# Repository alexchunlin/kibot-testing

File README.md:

<h1 align="center">EncoGo</h1>

<p align="center" width="100%">
  
</p>

***

<p align="center">
  
&nbsp; &nbsp; &nbsp; &nbsp;
  
</p>

***

## SPECIFICATIONS

| Parameter | Value | 
| --- | --- |
| Dimensions | 40.0 × 40.0 mm |

***

## DIRECTORY STRUCTURE

    .
    ├─ Computations       # Misc calculations
    ├─ HTML               # HTML files for generated webpage
    ├─ Images             # Pictures and renders
    │
    ├─ kibot_resources    # External resources for KiBot
    │  ├─ colors          # Color theme for KiCad
    │  ├─ fonts           # Fonts used in the project
    │  ├─ scripts         # External scripts used with KiBot
    │  └─ templates       # Templates for KiBot generated reports
    │
    ├─ kibot_yaml         # KiBot YAML config files
    ├─ KiRI               # KiRI (PCB diff viewer) files
    │
    ├─ lib                # KiCad footprint and symbol libraries
    │  ├─ 3d_models       # Component 3D models
    │  ├─ lib_fp          # Footprint libraries
    │  └─ lib_sym         # Symbol libraries
    │
    ├─ Logos              # Logos
    │
    ├─ Manufacturing      # Assembly and fabrication documents
    │  ├─ Assembly        # Assembly documents (BoM, pos, notes)
    │  │
    │  └─ Fabrication     # Fabrication documents (ZIP, notes)
    │     ├─ Drill Tables # CSV drill tables
    │     └─ Gerbers      # Gerbers
    │
    ├─ Report             # Reports for ERC/DRC
    ├─ Schematic          # PDF of schematic
    ├─ Templates          # Title block templates
    ├─ Testing
    │  └─ Testpoints      # Testpoints tables      
    │
    └─ Variants           # Outputs for assembly variants

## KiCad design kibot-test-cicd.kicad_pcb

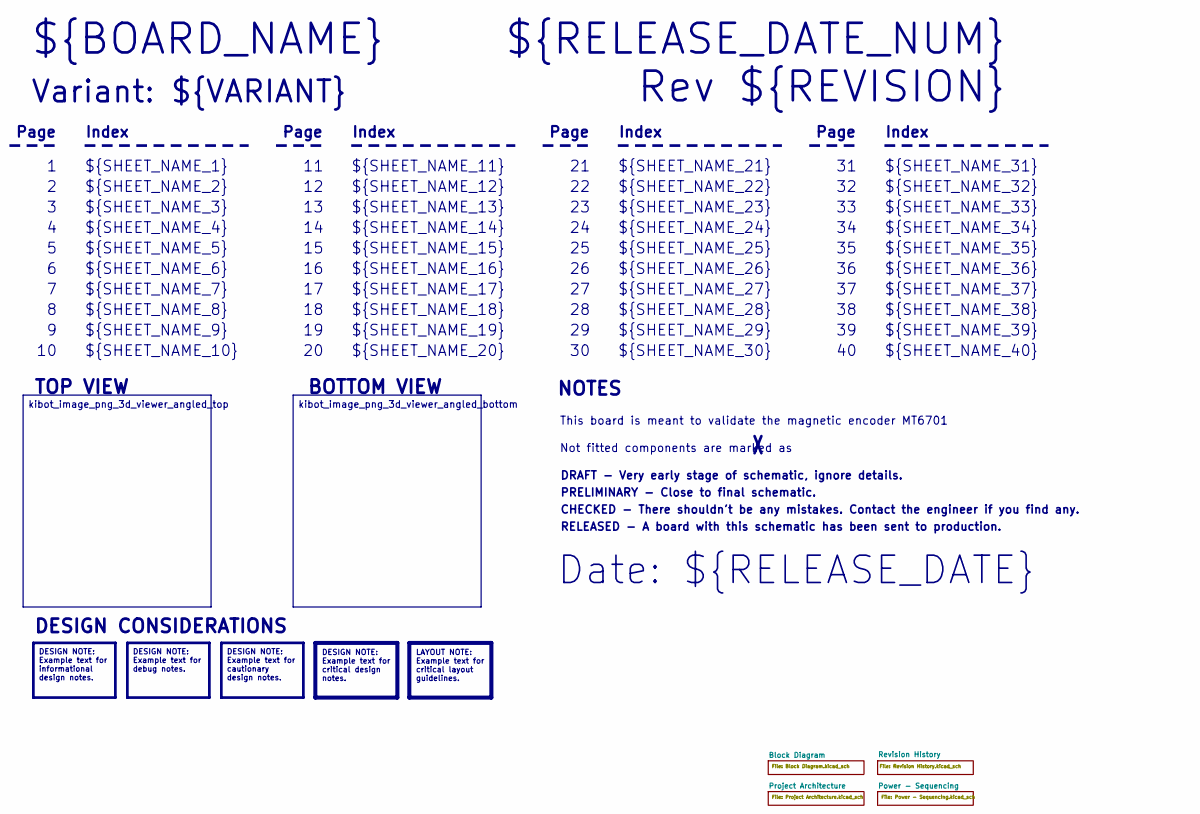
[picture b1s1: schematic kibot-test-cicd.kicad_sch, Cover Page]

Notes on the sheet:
Variant: ${VARIANT}
RELEASED - A board with this schematic has been sent to production.
${SHEET_NAME_24}
Index
Page
PRELIMINARY - Close to final schematic.
${SHEET_NAME_22}
DRAFT - Very early stage of schematic, ignore details.
${SHEET_NAME_12}
${SHEET_NAME_8}
${SHEET_NAME_2}
${SHEET_NAME_5}
${SHEET_NAME_20}
${SHEET_NAME_23}
${RELEASE_DATE_NUM}
${SHEET_NAME_35}
Not fitted components are marked as
${SHEET_NAME_11}
${SHEET_NAME_6}
${SHEET_NAME_37}
${SHEET_NAME_26}
${SHEET_NAME_36}
Rev ${REVISION}
${SHEET_NAME_15}
CHECKED - There shouldn't be any mistakes. Contact the engineer if you find any.
BOTTOM VIEW
${SHEET_NAME_14}
${SHEET_NAME_21}
${SHEET_NAME_17}
${SHEET_NAME_18}
Date: ${RELEASE_DATE}
${SHEET_NAME_7}
${SHEET_NAME_31}
${BOARD_NAME}
NOTES
${SHEET_NAME_40}
${SHEET_NAME_39}
${SHEET_NAME_32}
${SHEET_NAME_1}
${SHEET_NAME_9}

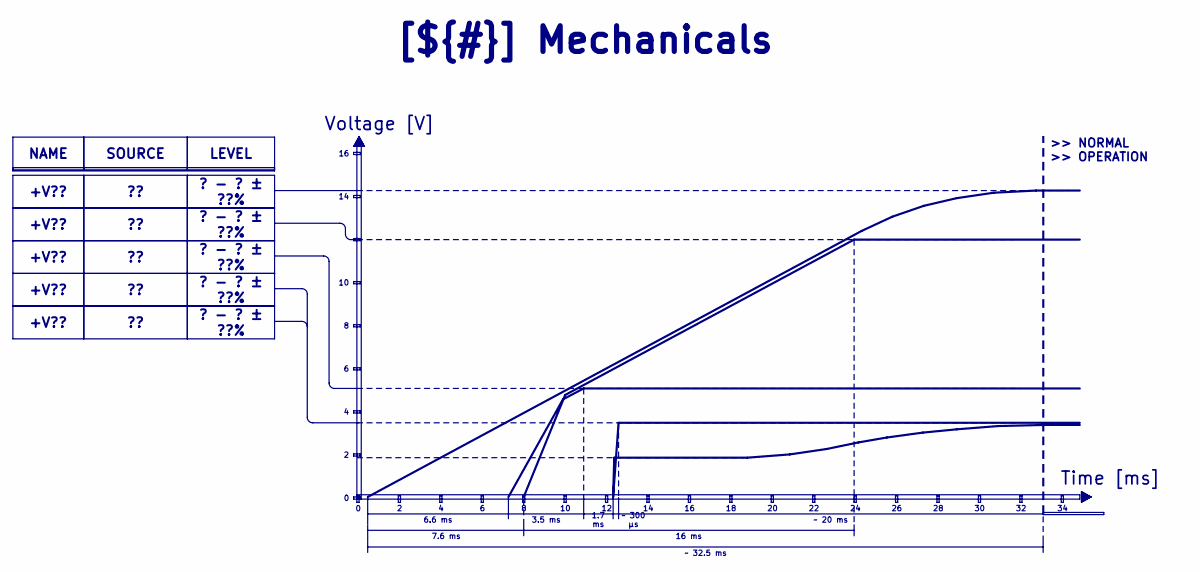
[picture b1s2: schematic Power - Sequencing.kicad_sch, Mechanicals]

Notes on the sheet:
Voltage [V]
>> NORMAL >> OPERATION
Time [ms]
3.5 ms
7.6 ms
? - ? ± ??%
~ 300 μs
1.7 ms
16 ms
+V??
LEVEL
NAME
~ 20 ms
SOURCE
[${#}] ${TITLE}
6.6 ms
~ 32.5 ms

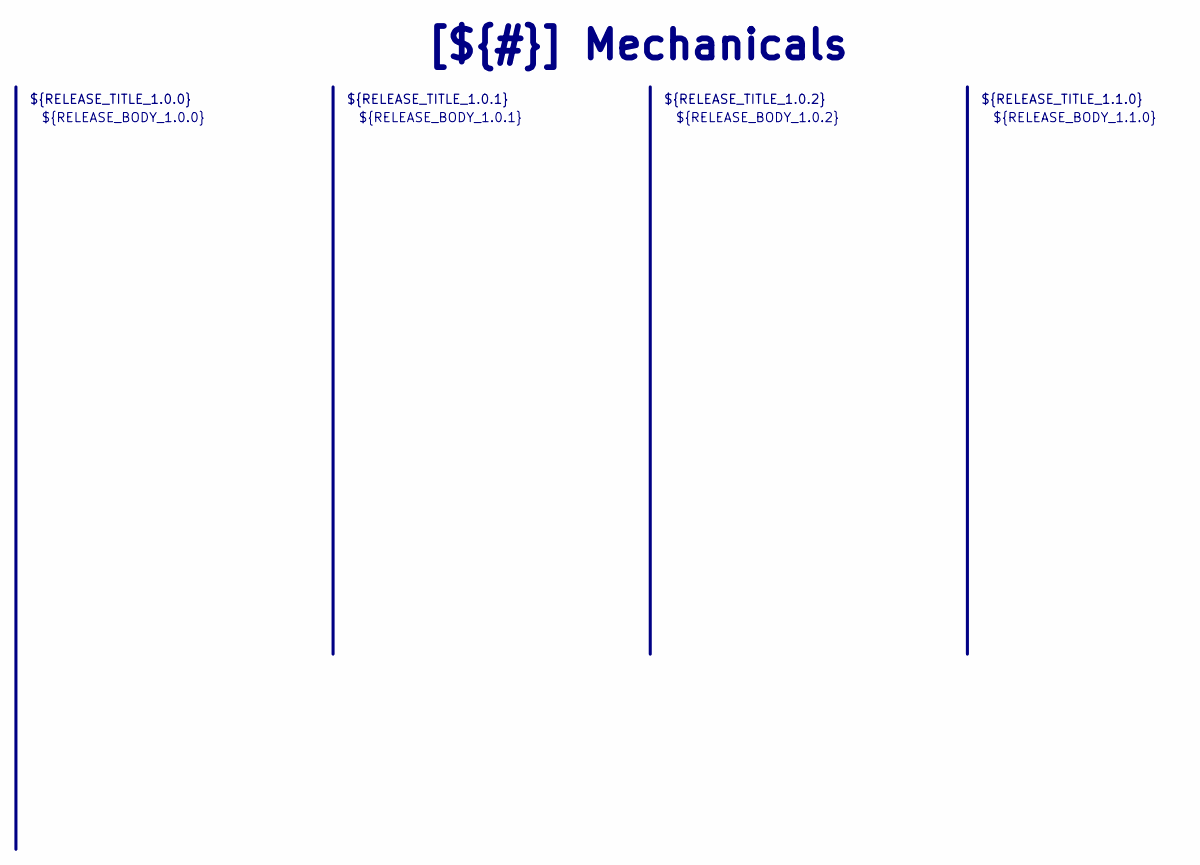
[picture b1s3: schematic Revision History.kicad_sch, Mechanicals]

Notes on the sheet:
${RELEASE_BODY_1.1.0}
[${#}] ${TITLE}
${RELEASE_BODY_1.0.0}
${RELEASE_TITLE_1.0.2}
${RELEASE_BODY_1.0.2}
${RELEASE_BODY_1.0.1}
${RELEASE_TITLE_1.0.0}
${RELEASE_TITLE_1.0.1}
${RELEASE_TITLE_1.1.0}

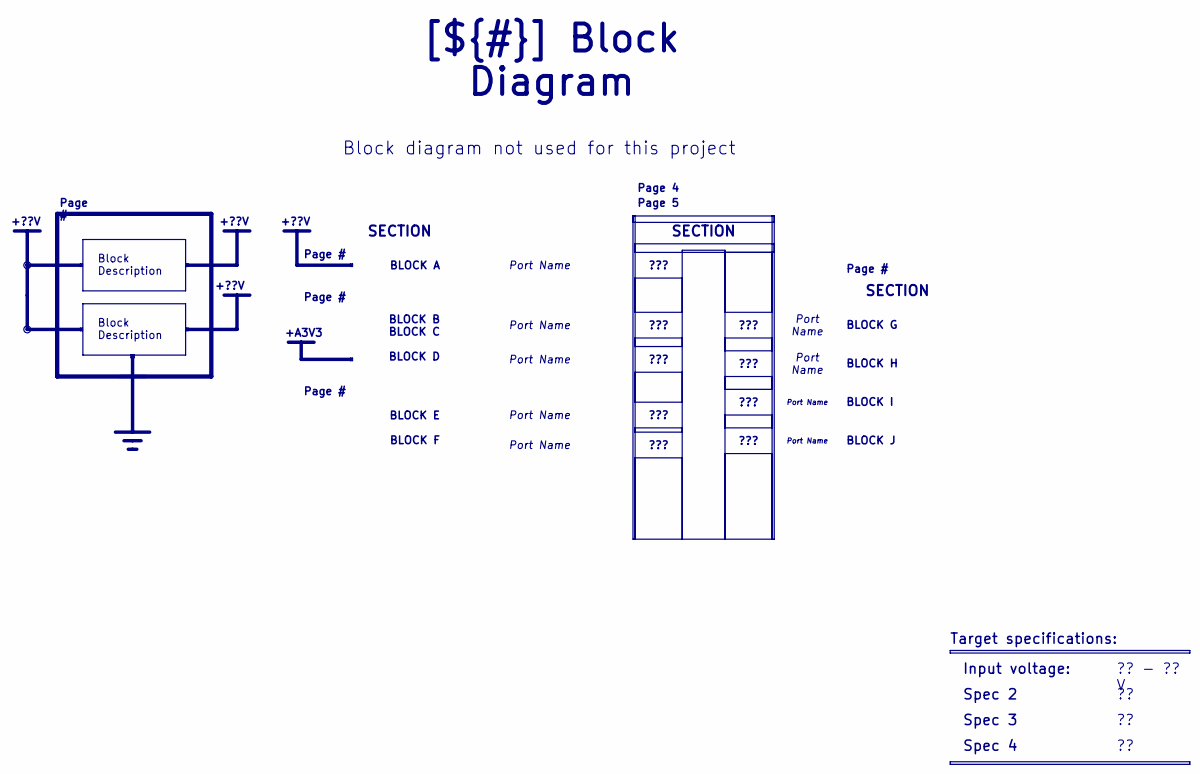
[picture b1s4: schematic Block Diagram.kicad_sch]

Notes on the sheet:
+??V
Block diagram not used for this project
+A3V3
SECTION
Spec 4
BLOCK H
BLOCK B BLOCK C BLOCK D
BLOCK I
?? - ?? V
Block Description
???
Port Name
BLOCK G
Page #
Page 4
[${#}] ${TITLE}
Input voltage:
Target specifications:
Spec 3
Spec 2
BLOCK A
BLOCK E BLOCK F
BLOCK J
Page 5

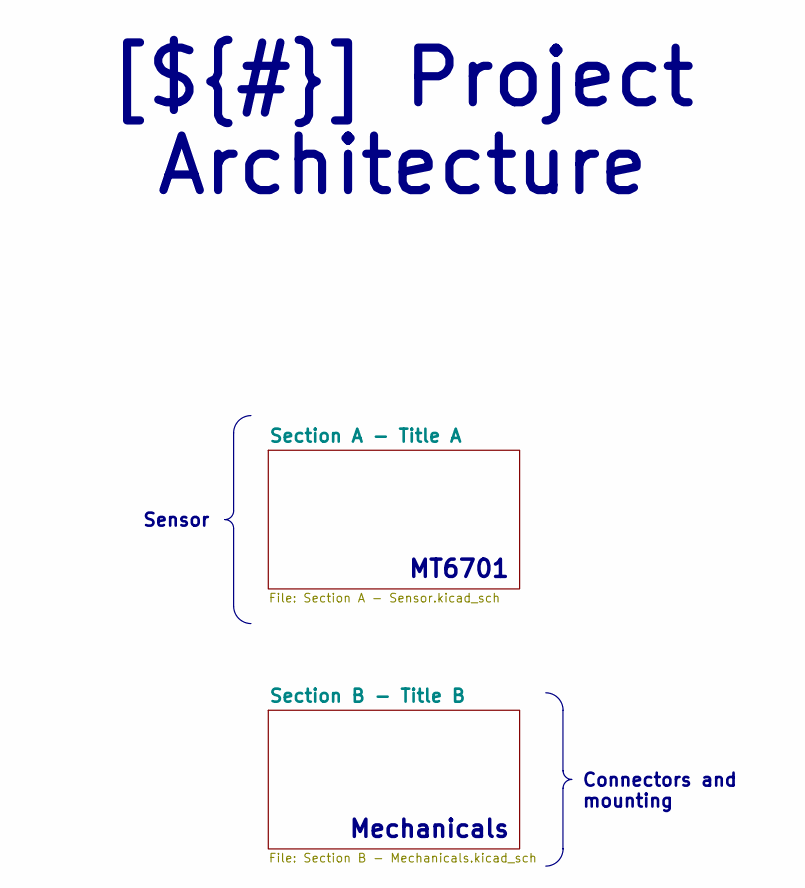
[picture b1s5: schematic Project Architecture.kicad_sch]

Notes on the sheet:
Mechanicals
MT6701
Sensor
Connectors and mounting
[${#}] ${TITLE}

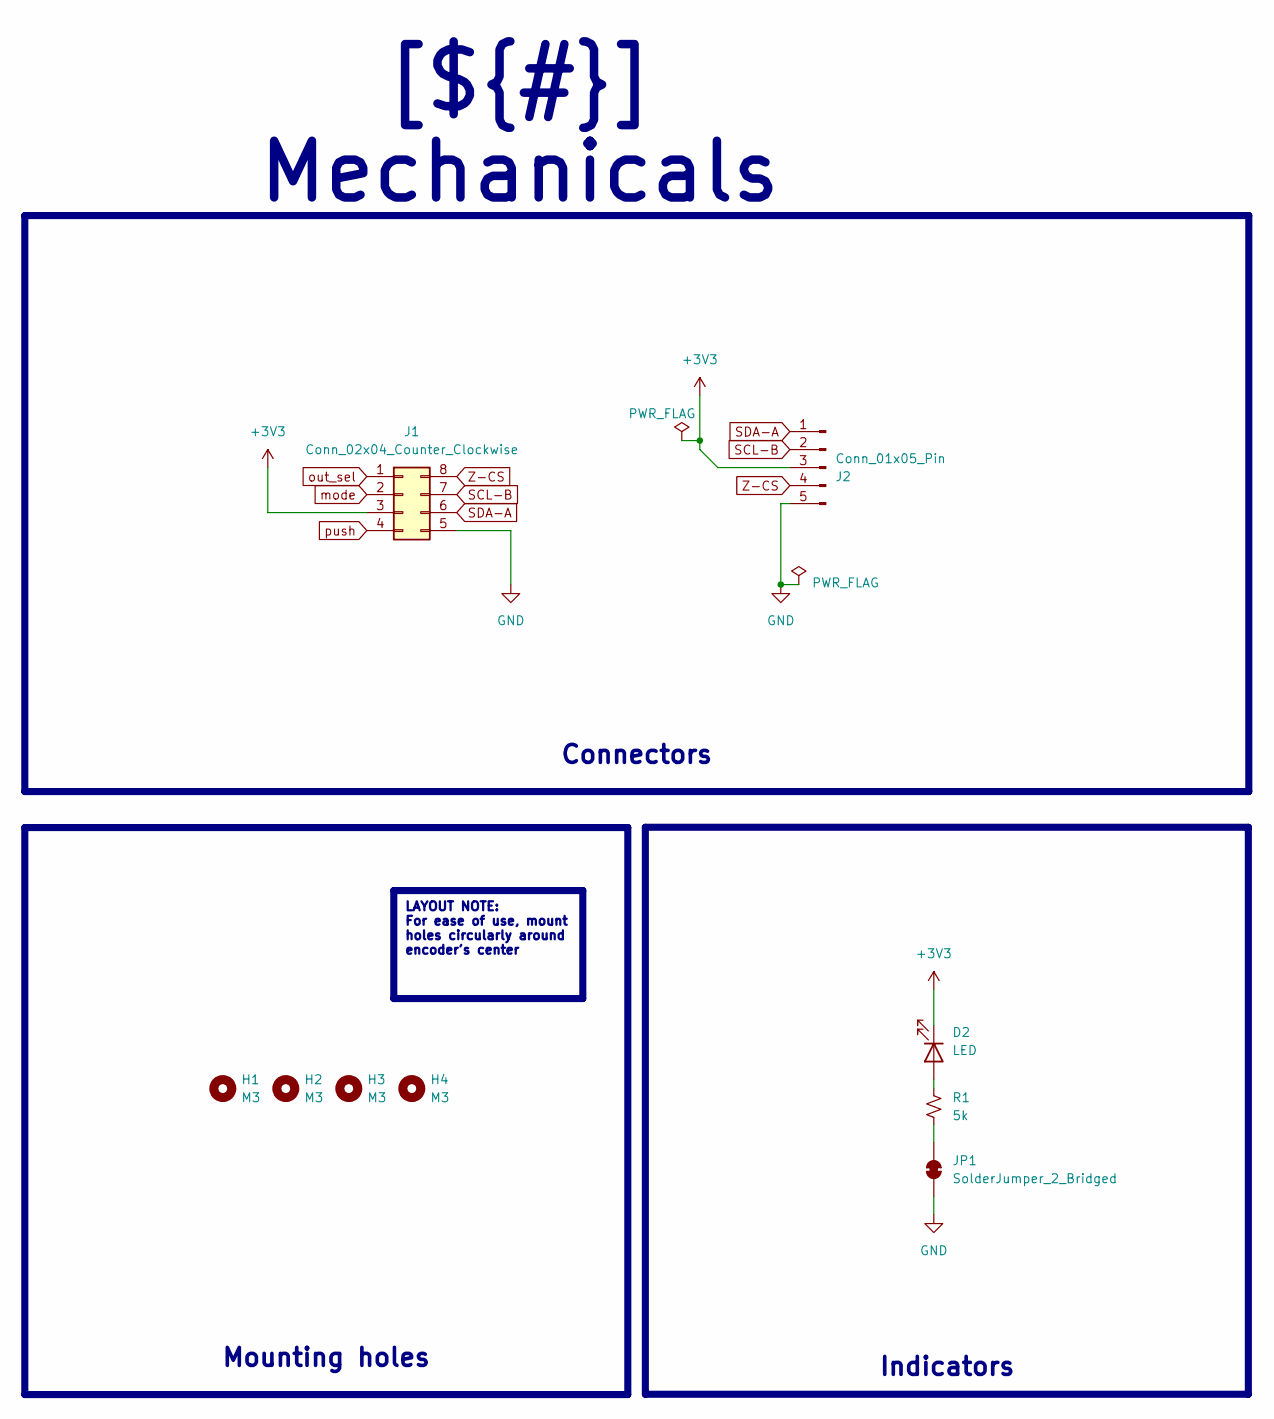
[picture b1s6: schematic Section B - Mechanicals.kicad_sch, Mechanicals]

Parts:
D2: LED; LED_0603_1608Metric
H1, H2, H3, H4: M3; MountingHole_3.2mm_M3
J1: Conn_02x04_Counter_Clockwise; PinHeader_2x04_P2.54mm_Vertical
J2: Conn_01x05_Pin; JST_SH_BM05B-SRSS-TB_1x05-1MP_P1.00mm_Vertical
JP1: SolderJumper_2_Bridged; SolderJumper-2_P1.3mm_Bridged_RoundedPad1.0x1.5mm
R1: 5k; R_0402_1005Metric

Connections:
+3V3: D2.1 (K), J1.3, J2.3; also elsewhere on the board
GND: J1.5, J2.5, JP1.1 (A); also elsewhere on the board
unnamed: D2.2 (A), R1.1
unnamed: JP1.2 (B), R1.2
SCL-B: J1.7, J2.2; also elsewhere on the board
SDA-A: J1.6, J2.1; also elsewhere on the board
Z-CS: J1.8, J2.4; also elsewhere on the board
mode: J1.2; also elsewhere on the board
out_sel: J1.1; also elsewhere on the board
push: J1.4; also elsewhere on the board

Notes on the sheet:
Indicators
[${#}] ${TITLE}
LAYOUT NOTE: For ease of use, mount holes circularly around encoder's center
Connectors
Mounting holes

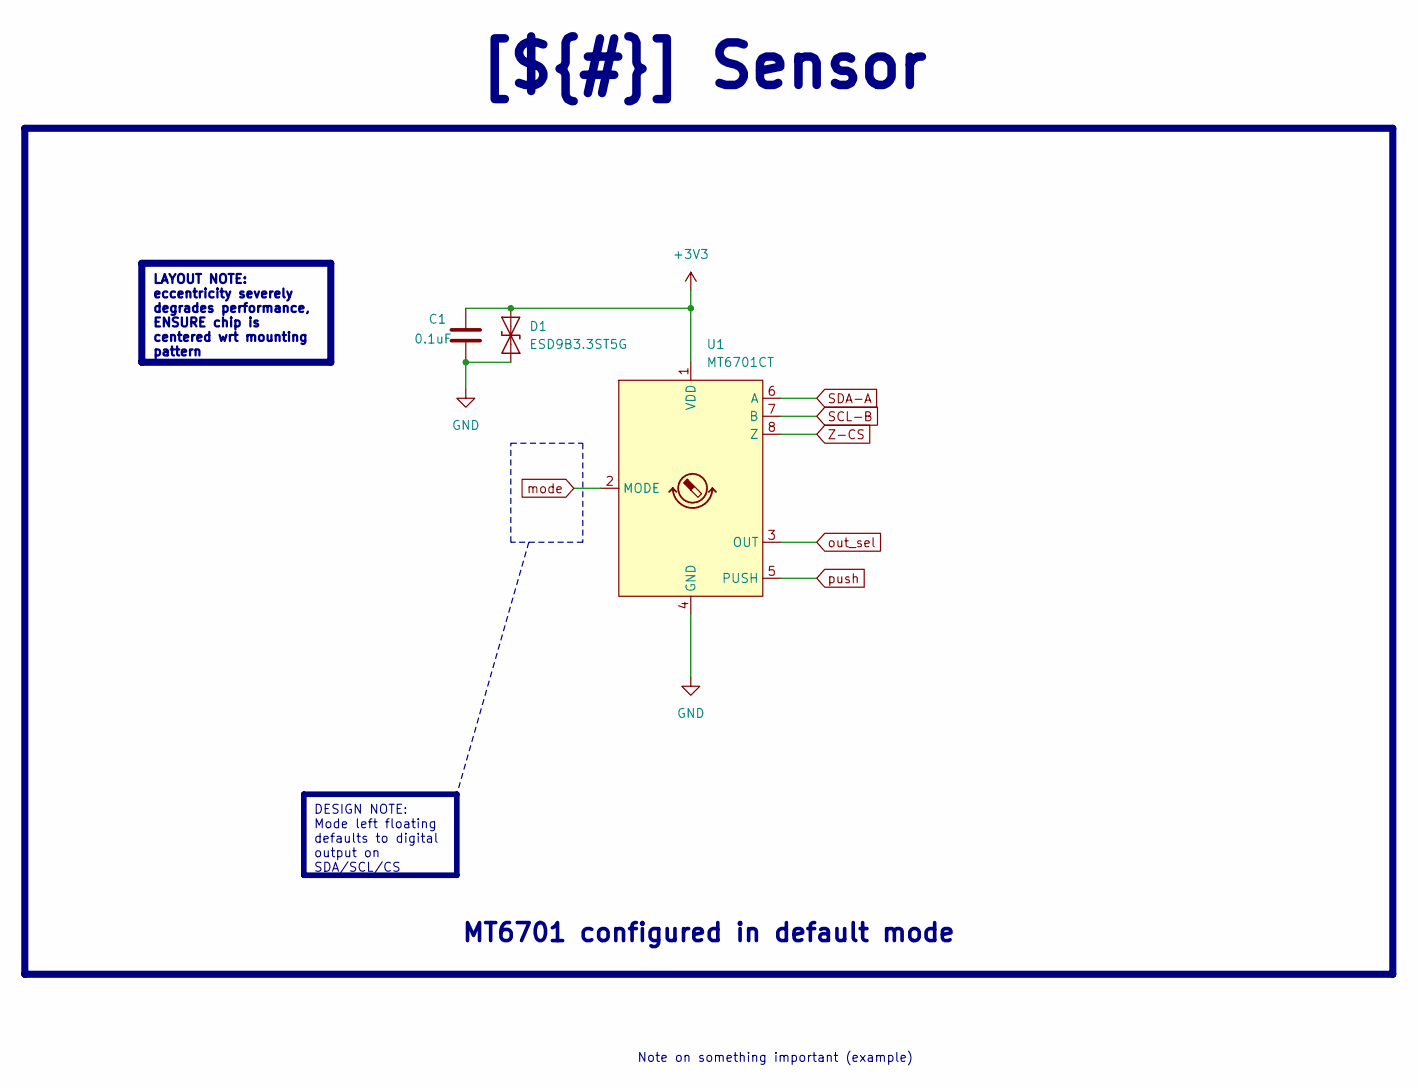
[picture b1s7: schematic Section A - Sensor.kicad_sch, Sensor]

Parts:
C1: 0.1uF; C_0603_1608Metric
D1: ESD9B3.3ST5G; D_SOD-923
U1: MT6701CT; SO-8_3.9x4.9mm_P1.27mm

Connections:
+3V3: C1.1, D1.2 (A2), U1.1 (VDD); also elsewhere on the board
GND: C1.2, D1.1 (A1), U1.4 (GND); also elsewhere on the board
SCL-B: U1.7 (B); also elsewhere on the board
SDA-A: U1.6 (A); also elsewhere on the board
Z-CS: U1.8 (Z); also elsewhere on the board
mode: U1.2 (MODE); also elsewhere on the board
out_sel: U1.3 (OUT); also elsewhere on the board
push: U1.5 (PUSH); also elsewhere on the board

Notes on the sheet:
Note on something important (example)
LAYOUT NOTE: eccentricity severely degrades performance, ENSURE chip is centered wrt mounting pattern
[${#}] ${TITLE}
MT6701 configured in default mode
DESIGN NOTE: Mode left floating defaults to digital output on SDA/SCL/CS

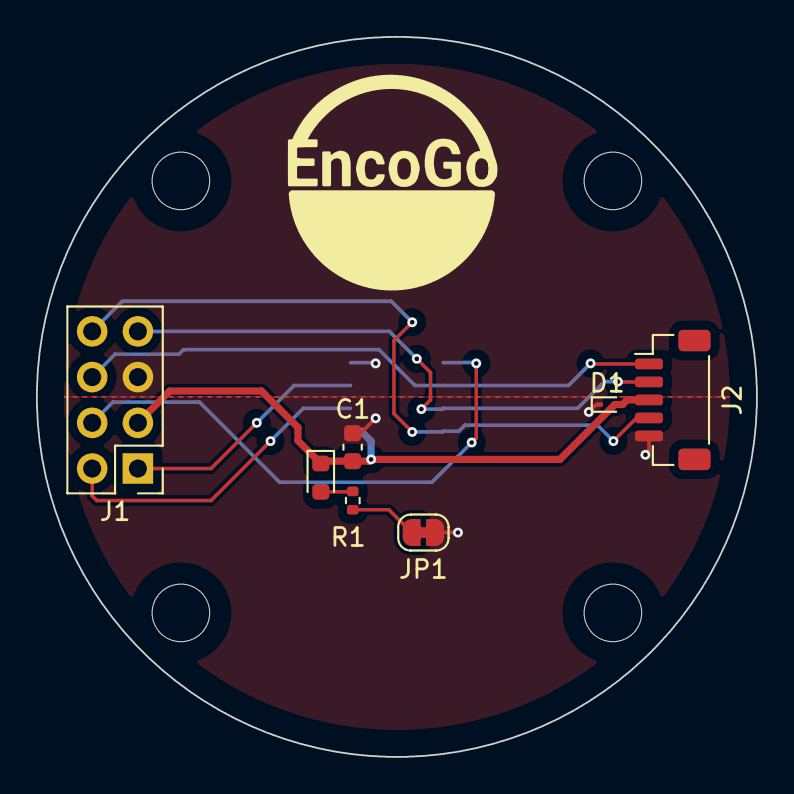
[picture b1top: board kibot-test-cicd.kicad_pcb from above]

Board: 2 copper layers, 40.0 x 40.0 mm, 12 parts (1 on the bottom side), 10 nets.

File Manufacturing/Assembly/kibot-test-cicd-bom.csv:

Row,Quantity Per PCB,References,Value,Datasheet,Footprint,Description,Manufacturer,Manufacturer Part Number,Supplier Part Number
1,1,C1,0.1uF,~,C_0603_1608Metric,Unpolarized capacitor,,,
2,1,D1,ESD9B3.3ST5G,https://www.onsemi.com/pub/Collateral/ESD9B-D.PDF,D_SOD-923,"ESD protection diode, 3.3Vrwm, SOD-923",,,
3,1,D2,LED,~,LED_0603_1608Metric,Light emitting diode,,,
4,2,J1 J2,Conn_02x04_Counter_Clockwise,~,PinHeader_2x04_P2.54mm_Vertical,"Generic connector, double row, 02x04, counter clockwise pin numbering scheme (similar to DIP package numbering), script generated (kicad-library-utils/schlib/autogen/connector/) Generic connector, single row, 01x05, script generated",,,
5,1,R1,5k,~,R_0402_1005Metric,"Resistor, small US symbol",,,
6,1,U1,MT6701CT,https://www.magntek.com.cn/upload/MT6701_Rev.1.5.pdf,SO-8_3.9x4.9mm_P1.27mm,"Hall Based Angle Position Encoder Sensor, I2C, SSI, ABZ & UVW interfaces, 3.3..5V supply, SOIC-8",,,

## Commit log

2026-01-12 added ci workflow file to root of project
2026-01-12 configured project metadata
2026-01-12 Update Outputs
2026-01-12 [added] completed initial sch design, move from draft to preliminary
2026-01-12 [bugfix] fixed J1 connector footprint and power indicator D2 polarity
2026-01-12 forcing push to tag head with version number
2026-01-12 Update CHANGELOG
2026-01-12 [PCB] added basic layout
2026-01-12 [PCB] added ground plane
2026-01-14 [PCB] finished layout
2026-01-14 minor adjustments
2026-01-14 [PROJECT] Preliminary -> Checked
2026-01-15 DRC violations fixed
2026-01-15 fixed ERC violations
2026-01-15 fixed the via sizes to match the HERL capabilities
2026-01-16 [PROJECT] Checked -> Released
2026-01-16 added dimensions to back of board for encoder height
2026-01-16 updated dimensions on layer B.Dimensions
